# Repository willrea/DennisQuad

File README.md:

# DennisQuad

Roughly based on https://github.com/jaw0/minicopter

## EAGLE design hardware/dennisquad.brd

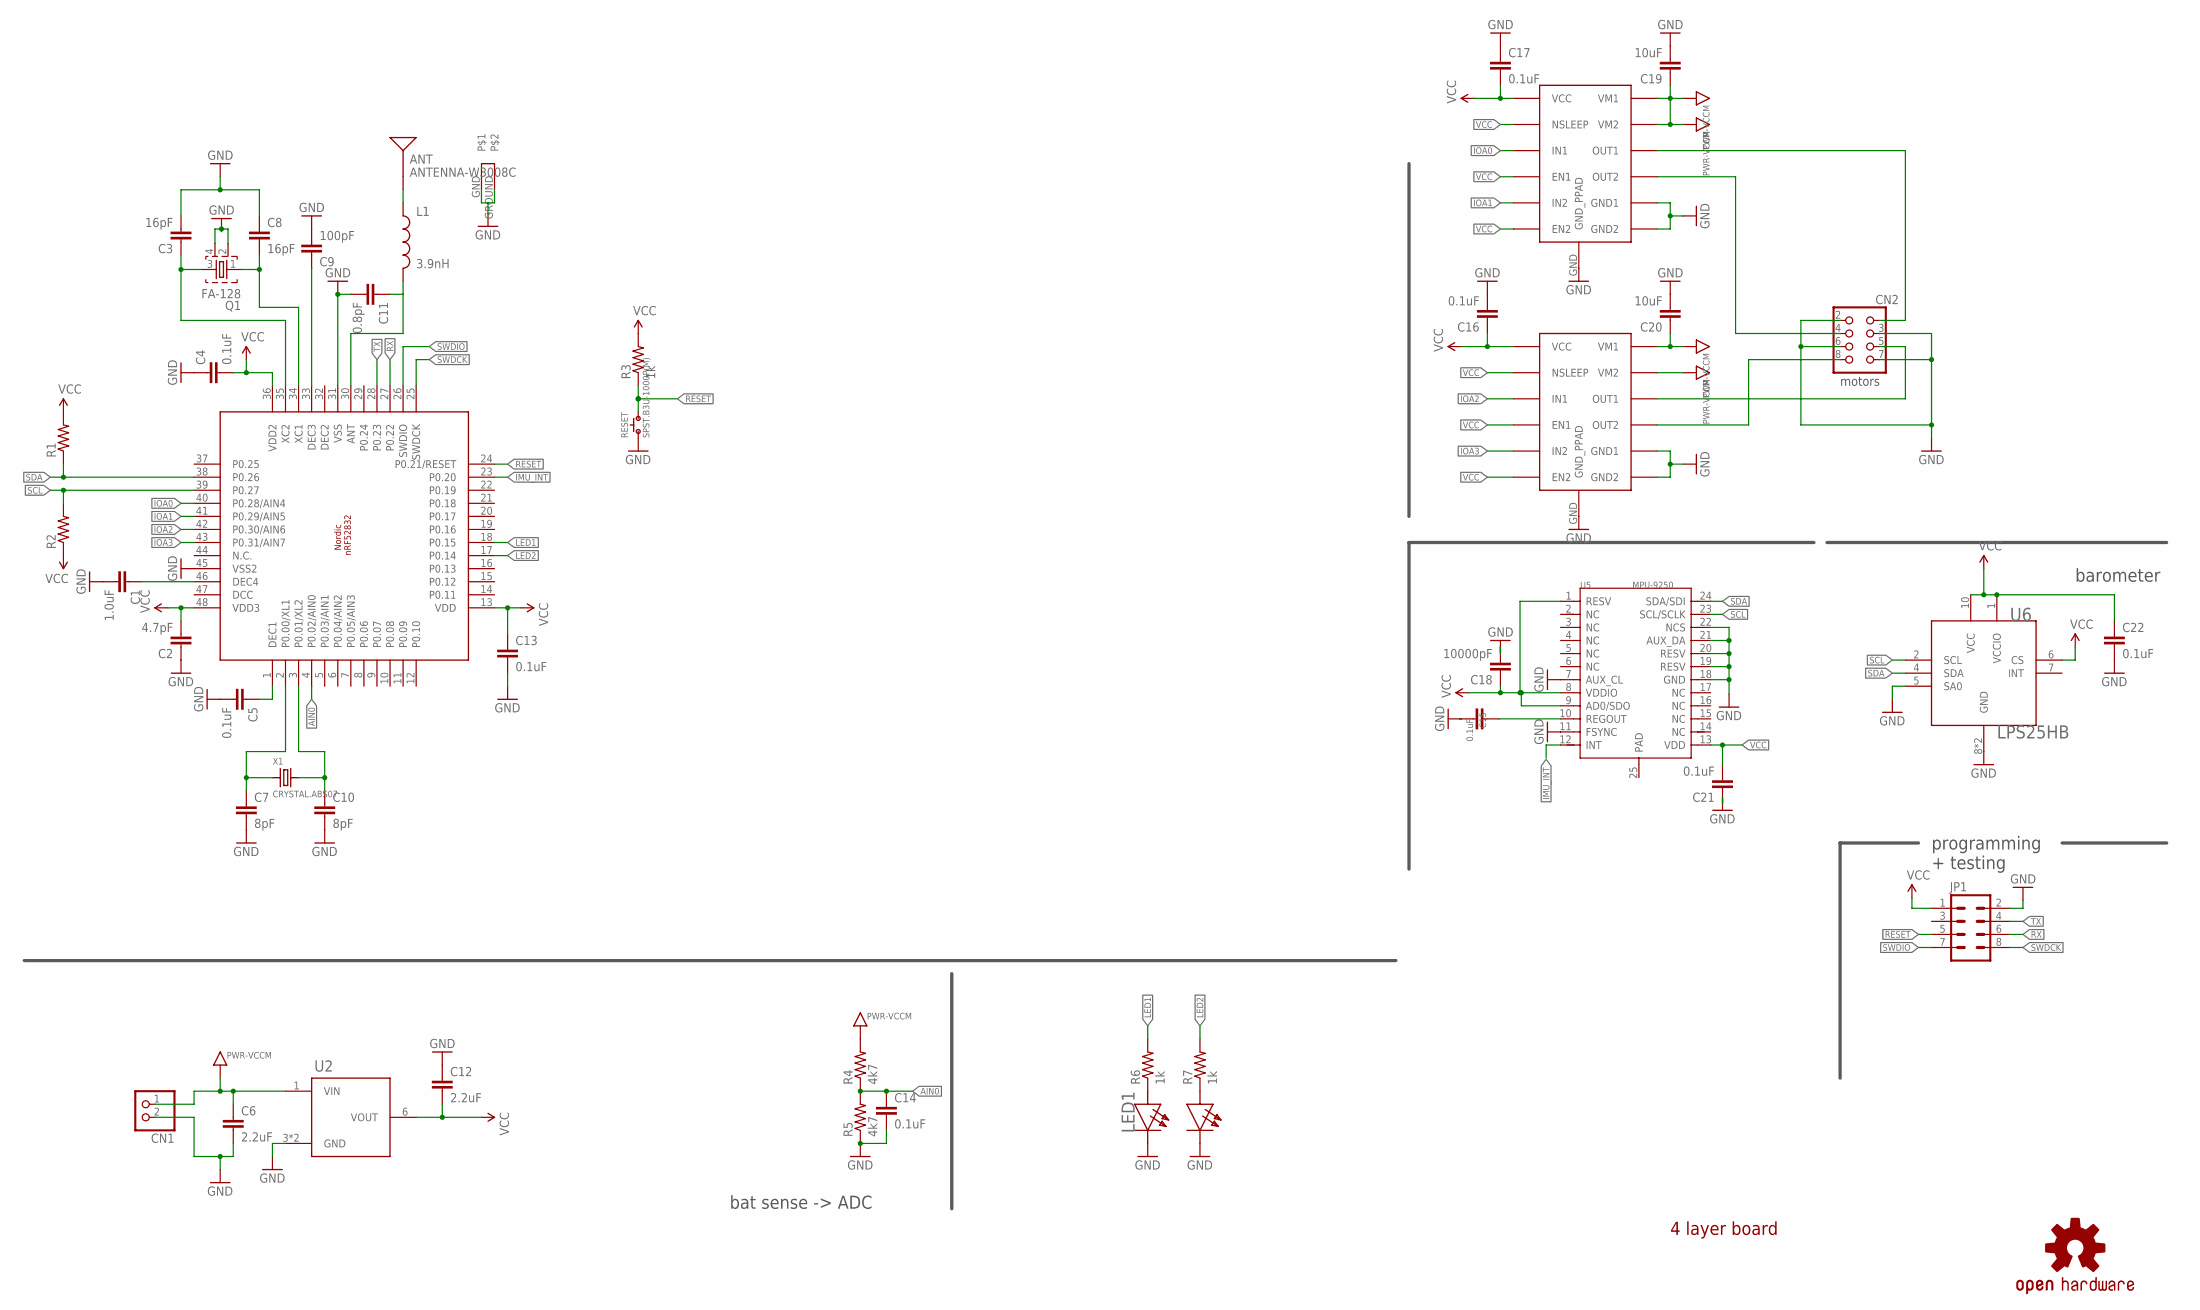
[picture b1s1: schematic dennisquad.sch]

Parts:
ANT: ANTENNA-W3008C
C1: 1.0uF; 0603-CAP
C2: 4.7pF; 0603-CAP
C3, C8: 16pF; 0402-CAP; MPN GRM1555C1H160GA01D
C4, C5, C13, C14, C15, C16, C17, C21, C22: 0.1uF; 0402-CAP; MPN CL05B104JO5NNNC
C6, C12: 2.2uF; 0402-CAP; MPN GRT155R61C225KE13D
C7, C10: 8pF; 0402-CAP; MPN GRM1555C1H8R0BA01D
C9: 100pF; 0402-CAP; MPN GRM1555C1H101JA01D
C11: 0.8pF; 0402-CAP; MPN GRM1555C2AR80BA01D
C18: 10000pF; 0402-CAP; MPN CL05B103KP5NNNC
C19, C20: 10uF; 0603-CAP; MPN C1206C106M4RACAUTO
CN1: JST_2PIN-THM; JST-PH-2-THM
CN2: HEADER-2X4; HEADER-2X04-THM
JP1: M04X2; 2X4
L1: 3.9nH; 0603; MPN AISC-0402-3N9J-T
LED1: LED-DUAL0805; SMD0805-DUAL; MPN APHBM2012QBDSURKC
LOGO1: OSHW-LOGOM; OSHW-LOGO-M
Q1: FA-128; MPN FA-128 32.0000MF20X-K3
R1, R2: RESISTOR0402; 0402-RES
R3, R6, R7: 1k; 0402-RES; MPN ERJ-2GEJ102X
R4, R5: 4k7; 0402-RES; MPN ERJ-PA2F4701X
RESET: SPST.B3U-1000P(M); B3U-1000P(M)
U1: NRF52832_QFN48; QFN48
U2: MCP1700T-3302E/MAY; 6-VDFN; MPN MCP1700T-3302E/MAY
U3, U4: DRV8839; PWSON-N12
U5: MPU-9250; LEAD-QFN24
U6: LPS25HB; HLGA10L
X1: CRYSTAL.ABS07; ABS07; MPN ABS07-120-32.768KHZ-T

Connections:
AIN0: C14.1, R4.1, R5.2, U1.4 (P0.02/AIN0)
DCC: U1.47 (DCC)
DEC2: U1.32 (DEC2)
GND: ANT.GND, ANT.GROUND, C1.2, C2.1, C3.2, C4.1, C5.2, C6.2, C7.2, C8.1, C9.2, C10.2, C11.2, C12.1, C13.2, C14.2, C15.2, C16.2, C17.1, C18.2, C19.2, C20.2, C21.1, C22.2, CN1.2 (1), CN2.2, CN2.3, CN2.6, CN2.7, JP1.2, LED1.2 (CB), LED1.3 (CR), Q1.2, Q1.4, R5.1, RESET.1, U1.31 (VSS), U1.45 (VSS2), U2.3 (GND), U2.P$1 (GND), U3.GND (GND_PPAD), U3.P$5 (GND1), U3.P$6 (GND2), U4.GND (GND_PPAD), U4.P$5 (GND1), U4.P$6 (GND2), U5.7 (AUX_CL), U5.11 (FSYNC), U5.18 (GND), U5.19 (RESV), U5.20 (RESV), U5.21 (AUX_DA), U5.22 (NCS), U6.5 (SA0), U6.8 (GND), U6.9 (GND)
IMU_INT: U1.23 (P0.20), U5.12 (INT)
IOA0: U1.40 (P0.28/AIN4), U3.P$9 (IN1)
IOA1: U1.41 (P0.29/AIN5), U3.P$11 (IN2)
IOA2: U1.42 (P0.30/AIN6), U4.P$9 (IN1)
IOA3: U1.43 (P0.31/AIN7), U4.P$11 (IN2)
LED1: R6.2, U1.18 (P0.15)
LED2: R7.2, U1.17 (P0.14)
unnamed: C15.1, U5.10 (REGOUT)
unnamed: C7.1, U1.2 (P0.00/XL1), X1.1
unnamed: LED1.1 (AB), R6.1
unnamed: LED1.4 (AR), R7.1
unnamed: CN2.1, U3.P$3 (OUT1)
unnamed: CN2.4, U3.P$4 (OUT2)
unnamed: ANT.FEED (SIGNAL), L1.1
unnamed: CN2.5, U4.P$3 (OUT1)
unnamed: CN2.8, U4.P$4 (OUT2)
unnamed: C10.1, U1.3 (P0.01/XL2), X1.2
unnamed: C1.1, U1.46 (DEC4)
unnamed: C5.1, U1.1 (DEC1)
unnamed: C9.1, U1.33 (DEC3)
unnamed: C8.2, Q1.1, U1.34 (XC1)
unnamed: C3.1, Q1.3, U1.35 (XC2)
unnamed: C11.1, L1.2, U1.30 (ANT)
RESET: JP1.5, R3.1, RESET.2, U1.24 (P0.21/RESET)
RX: JP1.6, U1.27 (P0.22)
SCL: R2.2, U1.39 (P0.27), U5.23 (SCL/SCLK), U6.2 (SCL)
SDA: R1.1, U1.38 (P0.26), U5.24 (SDA/SDI), U6.4 (SDA)
SWDCK: JP1.8, U1.25 (SWDCK)
SWDIO: JP1.7, U1.26 (SWDIO)
TX: JP1.4, U1.28 (P0.23)
VCC: C2.2, C4.2, C12.2, C13.1, C16.1, C17.2, C18.1, C21.2, C22.1, JP1.1, R1.2, R2.1, R3.2, U1.13 (VDD), U1.36 (VDD2), U1.48 (VDD3), U2.6 (VOUT), U3.P$7 (VCC), U3.P$8 (NSLEEP), U3.P$10 (EN1), U3.P$12 (EN2), U4.P$7 (VCC), U4.P$8 (NSLEEP), U4.P$10 (EN1), U4.P$12 (EN2), U5.1 (RESV), U5.8 (VDDIO), U5.9 (AD0/SDO), U5.13 (VDD), U6.1 (VCCIO), U6.6 (CS), U6.10 (VCC)
VCCM: C6.1, C19.1, C20.1, CN1.1 (2), R4.2, U2.1 (VIN), U3.P$1 (VM1), U3.P$2 (VM2), U4.P$1 (VM1), U4.P$2 (VM2)

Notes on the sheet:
programming + testing
bat sense -> ADC
motors
barometer
4 layer board

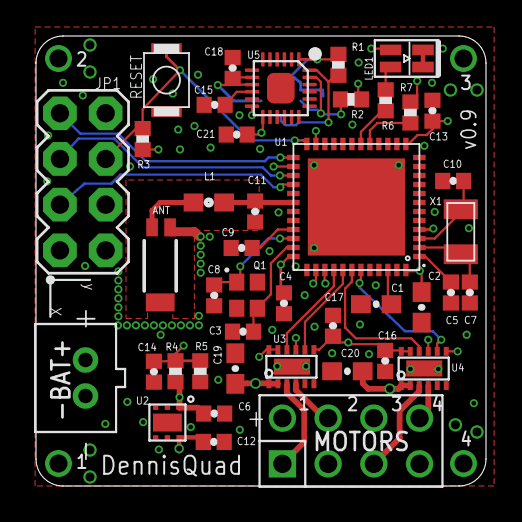
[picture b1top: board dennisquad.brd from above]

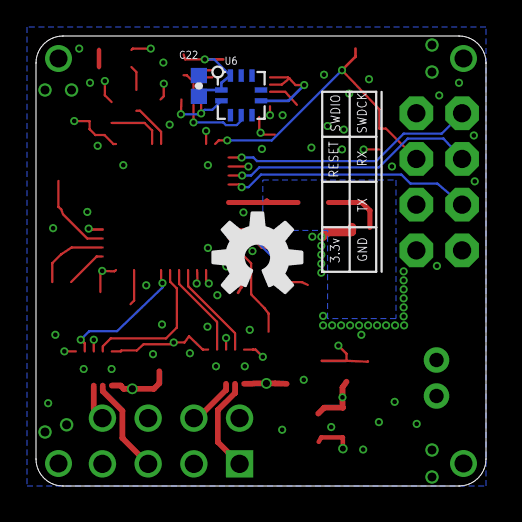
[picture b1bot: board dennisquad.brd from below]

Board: 4 copper layers, 25.0 x 25.0 mm, 45 parts (3 on the bottom side), 34 nets.

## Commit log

2015-12-23 Add license
2016-01-03 Add gitignore
2016-01-03 Move License file
2016-01-03 Version 0.9
2016-01-03 Silkscreen cleanup
2016-01-03 Minor changes
2016-01-03 Minor fixes

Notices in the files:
parts and their libraries:
SparkFun-Capacitors: Licensing: Creative Commons ShareAlike 4.0 International - https://creativecommons.org/licenses/by-sa/4.0
SparkFun-RF: Licensing: CC v3.0 Share-Alike You are welcome to use this library for commercial purposes.
